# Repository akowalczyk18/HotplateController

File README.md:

# Hotplate Controller

#### Hotplate controller for low cost reflow soldering
#### Will be adding more details of other system components

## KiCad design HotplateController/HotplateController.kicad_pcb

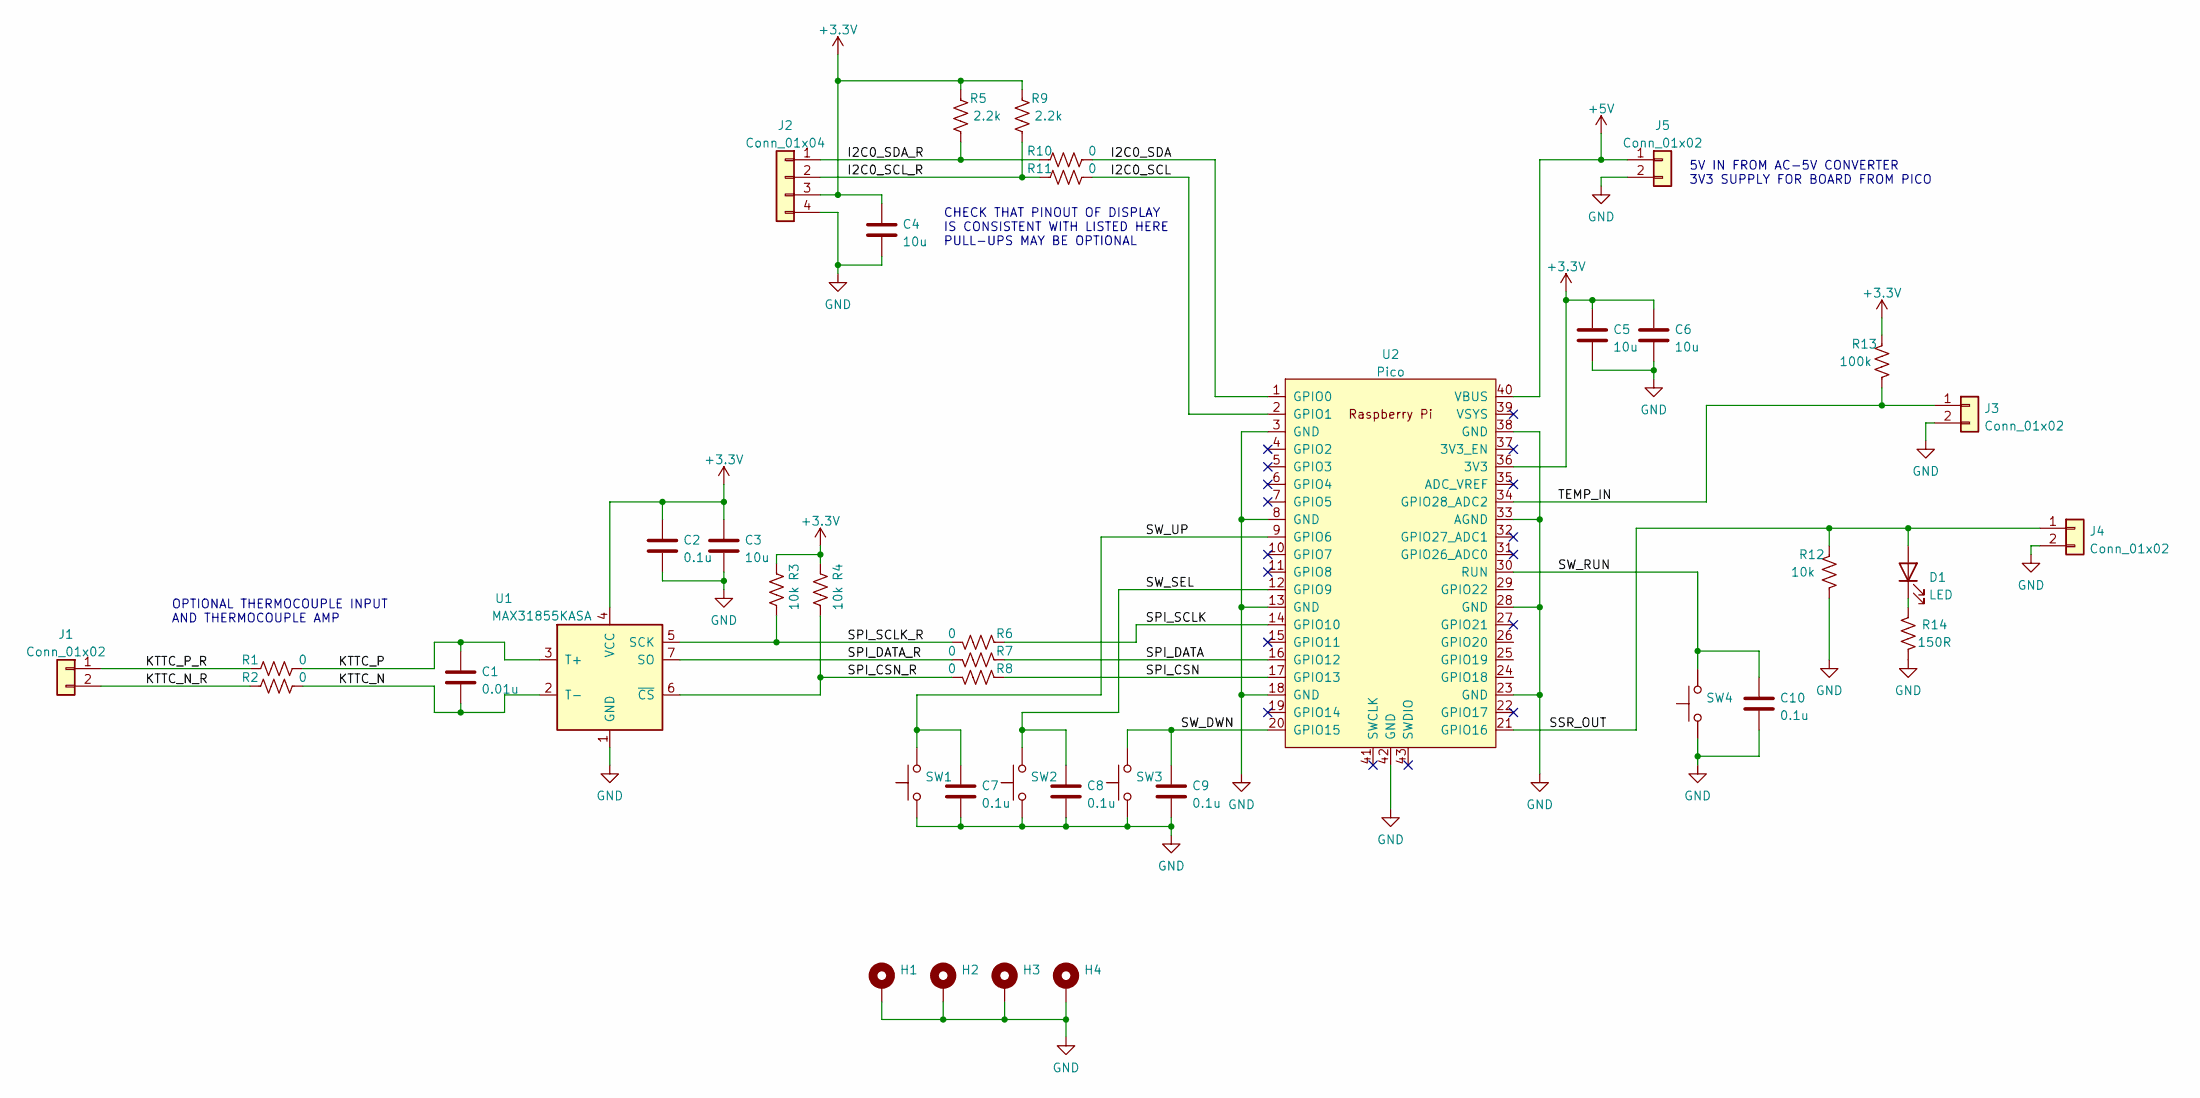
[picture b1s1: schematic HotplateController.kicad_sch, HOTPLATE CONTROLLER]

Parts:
C1: 0.01u; C_0603_1608Metric
C2, C7, C8, C9, C10: 0.1u; C_0603_1608Metric
C3, C4, C5, C6: 10u; C_0805_2012Metric_Pad1.18x1.45mm_HandSolder
D1: LED; LED_0603_1608Metric_Pad1.05x0.95mm_HandSolder
H1, H2, H3, H4: MountingHole_Pad; MountingHole_3.2mm_M3_ISO7380_Pad
J1, J5: Conn_01x02; TerminalBlock_MetzConnect_Type086_RT03402HBLC_1x02_P3.81mm_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
J2: Conn_01x04; PinHeader_1x04_P2.54mm_Vertical
J3, J4: Conn_01x02; PinHeader_1x02_P2.54mm_Vertical
R1, R2, R6, R7, R8, R10, R11: 0; R_0603_1608Metric_Pad0.98x0.95mm_HandSolder
R3, R4, R12: 10k; R_0603_1608Metric_Pad0.98x0.95mm_HandSolder
R5, R9: 2.2k; R_0603_1608Metric_Pad0.98x0.95mm_HandSolder
R13: 100k; R_0603_1608Metric_Pad0.98x0.95mm_HandSolder
R14: 150R; R_0603_1608Metric_Pad0.98x0.95mm_HandSolder
SW1, SW2, SW3, SW4: SW_Push; SW_PUSH_6mm
U1: MAX31855KASA; SOIC-8_3.9x4.9mm_P1.27mm
U2: Pico; RPi_Pico_SMD_TH

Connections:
+3V3: C2.1, C3.2, C4.1, C5.1, C6.1, J2.3, R3.1, R4.1, R5.1, R9.1, R13.1, U1.4 (VCC), U2.36 (3V3)
+5V: J5.1, U2.40 (VBUS)
/I2C0_SCL: R11.2, U2.2 (GPIO1)
/I2C0_SCL_R: J2.2, R9.2, R11.1
/I2C0_SDA: R10.2, U2.1 (GPIO0)
/I2C0_SDA_R: J2.1, R5.2, R10.1
/KTTC_N: C1.2, R2.2, U1.2 (T-)
/KTTC_N_R: J1.2, R2.1
/KTTC_P: C1.1, R1.2, U1.3 (T+)
/KTTC_P_R: J1.1, R1.1
/SPI_CSN: R8.1, U2.17 (GPIO13)
/SPI_CSN_R: R4.2, R8.2, U1.6 (~CS)
/SPI_DATA: R7.1, U2.16 (GPIO12)
/SPI_DATA_R: R7.2, U1.7 (SO)
/SPI_SCLK: R6.1, U2.14 (GPIO10)
/SPI_SCLK_R: R3.2, R6.2, U1.5 (SCK)
/SSR_OUT: D1.2 (A), J4.1, R12.1, U2.21 (GPIO16)
/SW_DWN: C9.1, SW3.2, U2.20 (GPIO15)
/SW_RUN: C10.1, SW4.2, U2.30 (RUN)
/SW_SEL: C8.1, SW2.2, U2.12 (GPIO9)
/SW_UP: C7.1, SW1.2, U2.9 (GPIO6)
/TEMP_IN: J3.1, R13.2, U2.34 (GPIO28_ADC2)
GND: C2.2, C3.1, C4.2, C5.2, C6.2, C7.2, C8.2, C9.2, C10.2, H1.1, H2.1, H3.1, H4.1, J2.4, J3.2, J4.2, J5.2, R12.2, R14.2, SW1.1, SW2.1, SW3.1, SW4.1, U1.1 (GND), U2.3 (GND), U2.8 (GND), U2.13 (GND), U2.18 (GND), U2.23 (GND), U2.28 (GND), U2.33 (AGND), U2.38 (GND), U2.42 (GND)
unnamed: D1.1 (K), R14.1

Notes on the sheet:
OPTIONAL THERMOCOUPLE INPUT AND THERMOCOUPLE AMP
CHECK THAT PINOUT OF DISPLAY IS CONSISTENT WITH LISTED HERE PULL-UPS MAY BE OPTIONAL
5V IN FROM AC-5V CONVERTER 3V3 SUPPLY FOR BOARD FROM PICO

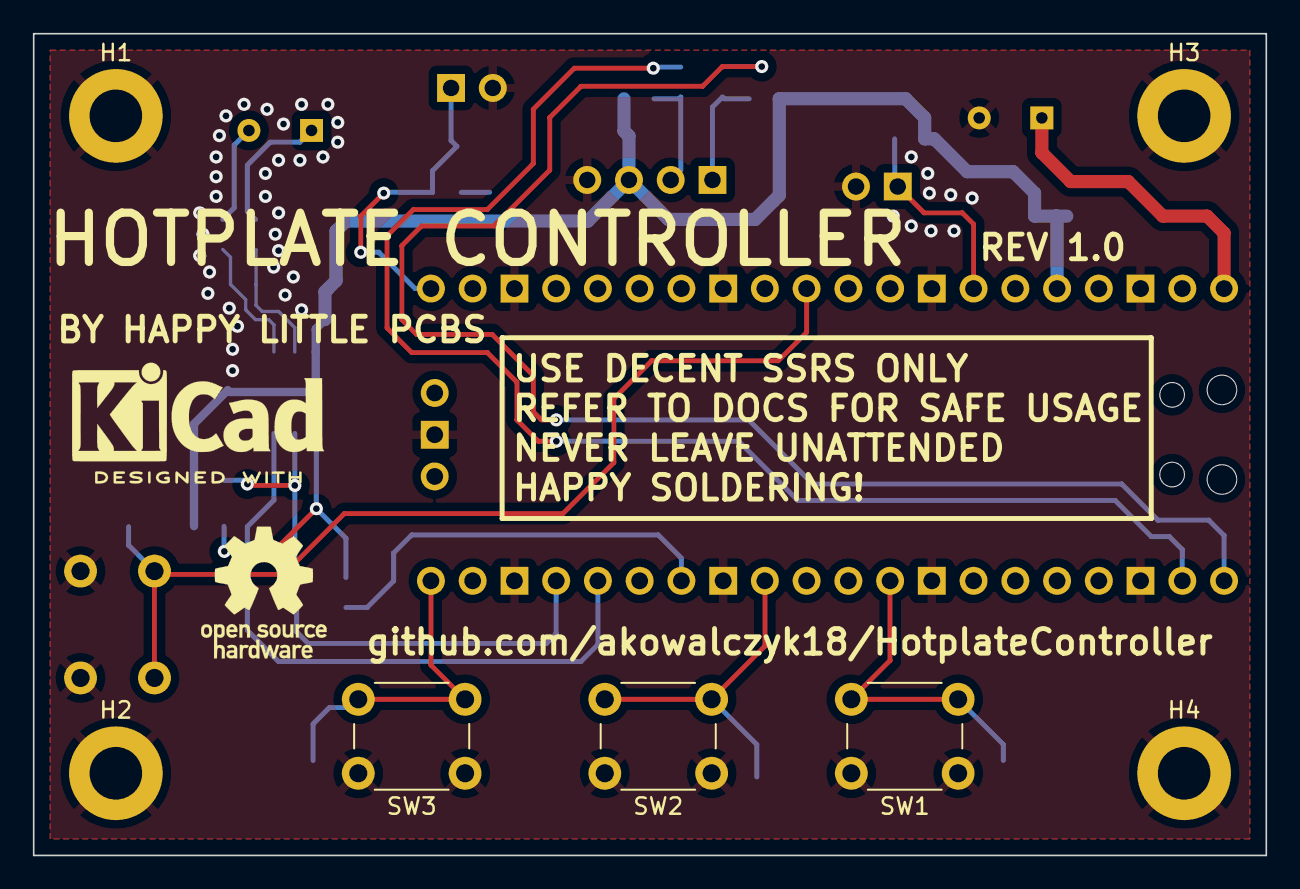
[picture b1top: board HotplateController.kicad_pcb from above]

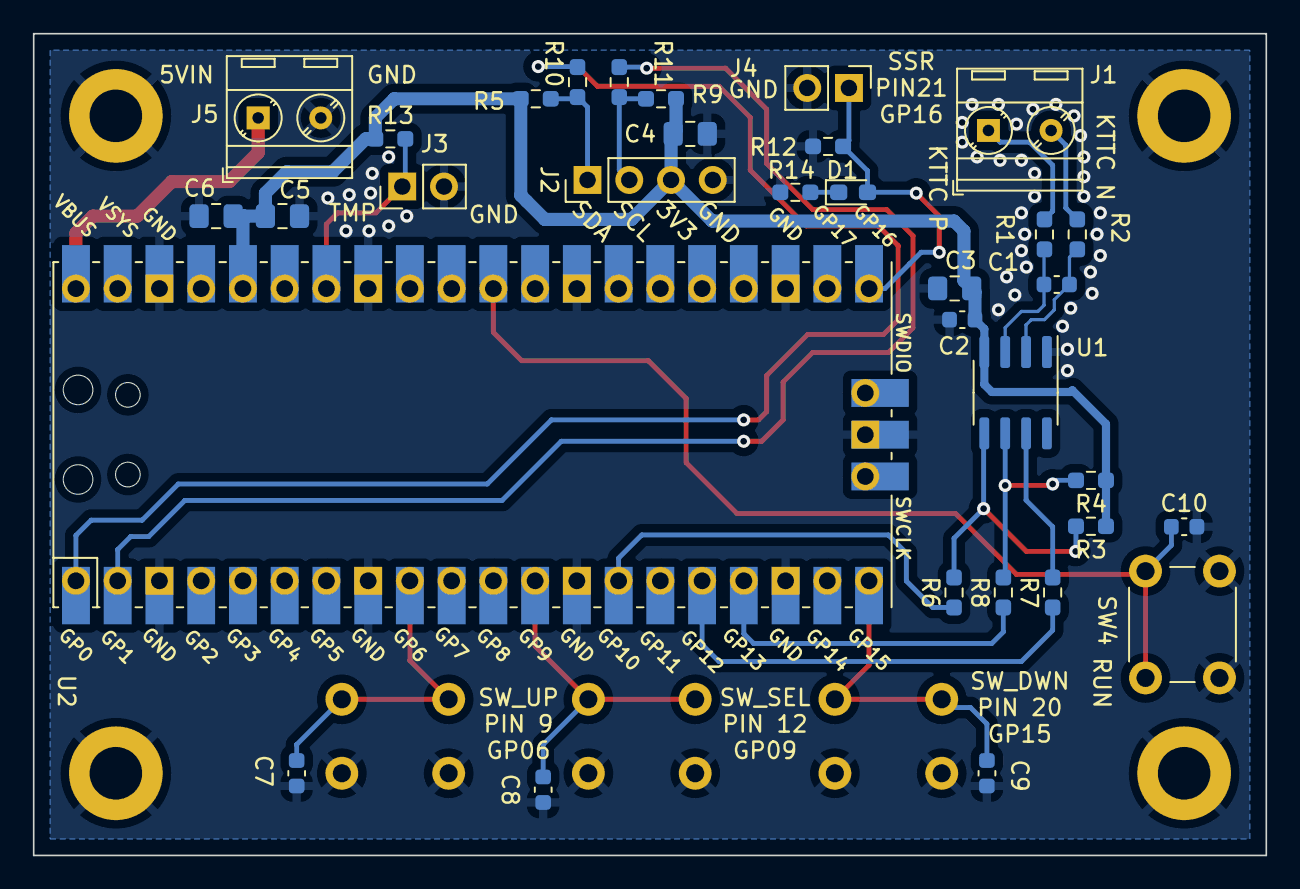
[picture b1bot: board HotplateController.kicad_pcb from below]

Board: 2 copper layers, 75.0 x 50.0 mm, 40 parts (33 on the bottom side), 24 nets.

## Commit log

2022-05-14 Create README.md
    Added README
2022-05-14 system_diagram.drawio
2022-05-14 Added system_diagram.drawio
2022-05-15 initial commit, added rpi pico, encoder, i2c display
2022-05-15 deleted backup drawing
2022-09-23 Added fab outputs, prep for pcbway contest
2023-01-25 significant code cleanup, implementation of setpoint, halfway towards PID implementation
2023-06-28 Update hotplate_firmware.ino
    Significant updates to PID and button code
    Known issues:
    -Huge overshoot on PID still, but better than it was, and able to hold temp a lot better. Increasing Kd helped significantly
    -Middle button is still touchy and can get multiple readings while holding. Need better debounce
